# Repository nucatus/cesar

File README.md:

# Cesar 3

**A 42-key ergonomic unibody keyboard, built around a modified Dvorak layout and a layer system designed for programming.**

Cesar 3 is the third iteration of a personal keyboard project. The goal is simple: type and write code all day without straining the hands, wrists or shoulders. Every decision in the design (the splayed key columns, the angled halves, the thumb clusters, the layout and the layers) serves that goal.

---

## Why it's ergonomic

- **Split, angled halves on a single board.** The two hands sit at shoulder-friendly angles, so the wrists stay straight and don't bend outward. It's a unibody, so there's still only one thing to carry and no cable between halves.
- **Column stagger and splay.** Keys follow the natural length of each finger: the middle-finger column sits highest, while the pinky and inner columns drop lower. Each column is also rotated to follow the arc the fingers make when they curl.
- **Fanned thumb clusters.** Each thumb gets three keys arranged on an arc. The thumbs, which do almost nothing on a regular keyboard, now handle Space, Enter, Esc, Tab and all the layer switching.
- **42 keys, no reaching.** With no number row, no function row and no far-away modifiers, every key is at most one row away from home. The rest comes from layers.
- **Home-row modifiers.** Shift, Alt, Ctrl and Cmd sit under the resting fingers (hold `A O E U` / `H T N S`), so shortcuts never need a pinky stretch to the corners.

## Modified Dvorak

The base layer is Dvorak. All the vowels sit on the left home row and the most common consonants on the right, so the hands alternate naturally and the fingers spend most of their time on the home row. A few changes adapt it to this board and to coding:

| Change | Why |
|---|---|
| `;` moved to the top-left and `'` to the bottom-left (swapped vs. standard Dvorak) | `;` is typed far more often than `'` in most languages, so it gets the easier spot |
| `L` and `D` swapped | Puts `L` on the right home row under the index finger |
| `/ = - [ ]` and friends removed from the base layer | They live on the dedicated symbol layer, close to home |
| Left outer column → `⌘C` `⌘V` `⌘Z` | One-key copy, paste and undo |
| Thumb keys are dual-role | Tap for `Esc` / `Enter` / `Space` / `Tab`, hold for a layer |

## Layers

On top of the base layer there are **three layers**, each held from a thumb key, so you never have to remember which layer is "on".

| Layer | Activated by | Contents |
|---|---|---|
| Base | — | Modified Dvorak + home-row mods |
| 1 · Numbers & Navigation | hold `Esc` or `Tab` | Digits on the left, arrows and paging on the right |
| 2 · Programming symbols | hold `Enter` or `Space` | Every bracket, operator and sigil you need for code |
| 3 · Function & media | hold either outer thumb key | `F1`–`F12`, media and volume controls |

### Base

### Layer 1: Numbers & navigation

- The most frequent digits (`0 1 2 3`) sit on the home row under the strongest fingers.
- The arrows go `← ↓ ↑ →` in a single row, the same order as Vim's `h j k l`.
- The layer is held from **either** thumb (`Esc` or `Tab`). While `Tab` holds it, the left thumbs become `Del` and `Backspace`, so you can edit while you navigate.

### Layer 2: Programming symbols

This layer was designed for code:

- **Brackets are on the home row as mirrored pairs:** `{ ( ) } [ ]`. Opening and closing a block is a single roll across the fingers.
- **Operators sit together:** `- * & |` on the right home row and `= + ! $` on the left bottom row, so comparisons (`!=`, `==`, `&&`, `||`, `+=`, `->`) are short rolls.
- **Shell and path characters** (`~ / \ % ^ ` # @ ? _`) all sit within one row of home.
- It can be held from **either** thumb, so you can always use the hand opposite the symbol.

### Layer 3: Function & media

- `F1`–`F12` run along the top two rows, with home-row mods still available. This makes IDE shortcuts like `⇧F6` and `⌘F12` easy to reach.
- Previous, Play/Pause and Next are on the left home row, with volume just below.

### Tuning

The full keymap is in [`firmware/config/boards/shields/cesar/cesar.keymap`](firmware/config/boards/shields/cesar/cesar.keymap).

The home-row mods and layer-taps use ZMK's `balanced` hold-tap with **positional hold-trigger** (a mod only activates when the next key is on the opposite hand). They also use a 280 ms tapping term, a 150 ms `require-prior-idle` and a 175 ms quick-tap. Together these stop accidental modifiers while you type fast.

---

## Hardware

|  |  |
|---|---|
| Keys | 42 (36 alpha + 6 thumb); 40 × 1u, 2 × 1.5u |
| Switches | MX-style, hot-swappable (Kailh sockets) |
| Controller | nice!nano v2 (nRF52840), wireless via Bluetooth |
| Firmware | [ZMK](https://zmk.dev), shield `cesar` (in [`firmware/`](firmware)) |
| Matrix | 4 rows × 12 columns, `col2row`, SOD-123 diodes |
| Extras | Reset button, two indicator LEDs |
| Plates | Top (switch) plate + bottom plate, 304 × 118 mm |
| Design tools | KiCad 9 |

### PCB

The finished board from below, with the Kailh hot-swap sockets and SOD-123 diodes soldered on:

### Schematic

### Plates

The top plate holds the switches; the bottom plate closes the case. Both are ready to cut from the DXF files in [`cad/`](cad).

---

## Repository layout

```
cad/                 Top and bottom plate DXF files (laser / CNC ready)
pcb/                 KiCad project: schematic, PCB layout, project settings
firmware/            ZMK user config with the `cesar` shield and keymap
docs/images/         Images used in this README
```

## Building one

1. Order the PCB from the KiCad project in `pcb/` (export Gerbers from KiCad).
2. Cut the two plates from `cad/*.dxf` (acrylic, aluminium or FR4 all work).
3. Solder the 42 SOD-123 diodes, the hot-swap sockets, the reset button, the LEDs and the nice!nano v2.
4. Build the firmware: every push runs the GitHub Actions workflow, which builds `cesar` for `nice_nano_v2`. Download the `.uf2` from the run's artifacts, double-tap reset, and copy it onto the nice!nano.
5. Mount the plates with standoffs, add switches and keycaps.

## License

- **Hardware** (`pcb/`, `cad/`, and the images and documentation in this repository): Copyright (c) 2024 Alexandru Ionita, licensed under the [CERN Open Hardware Licence Version 2 – Strongly Reciprocal](LICENSE) (CERN-OHL-S-2.0). If you distribute a modified version of the design, or products made from one, you must publish your modified source under the same licence.
- **Firmware** (`firmware/`): [MIT](firmware/LICENSE). The ZMK shield files keep their original copyright from the ZMK Contributors.

Source location: https://github.com/nucatus/cesar

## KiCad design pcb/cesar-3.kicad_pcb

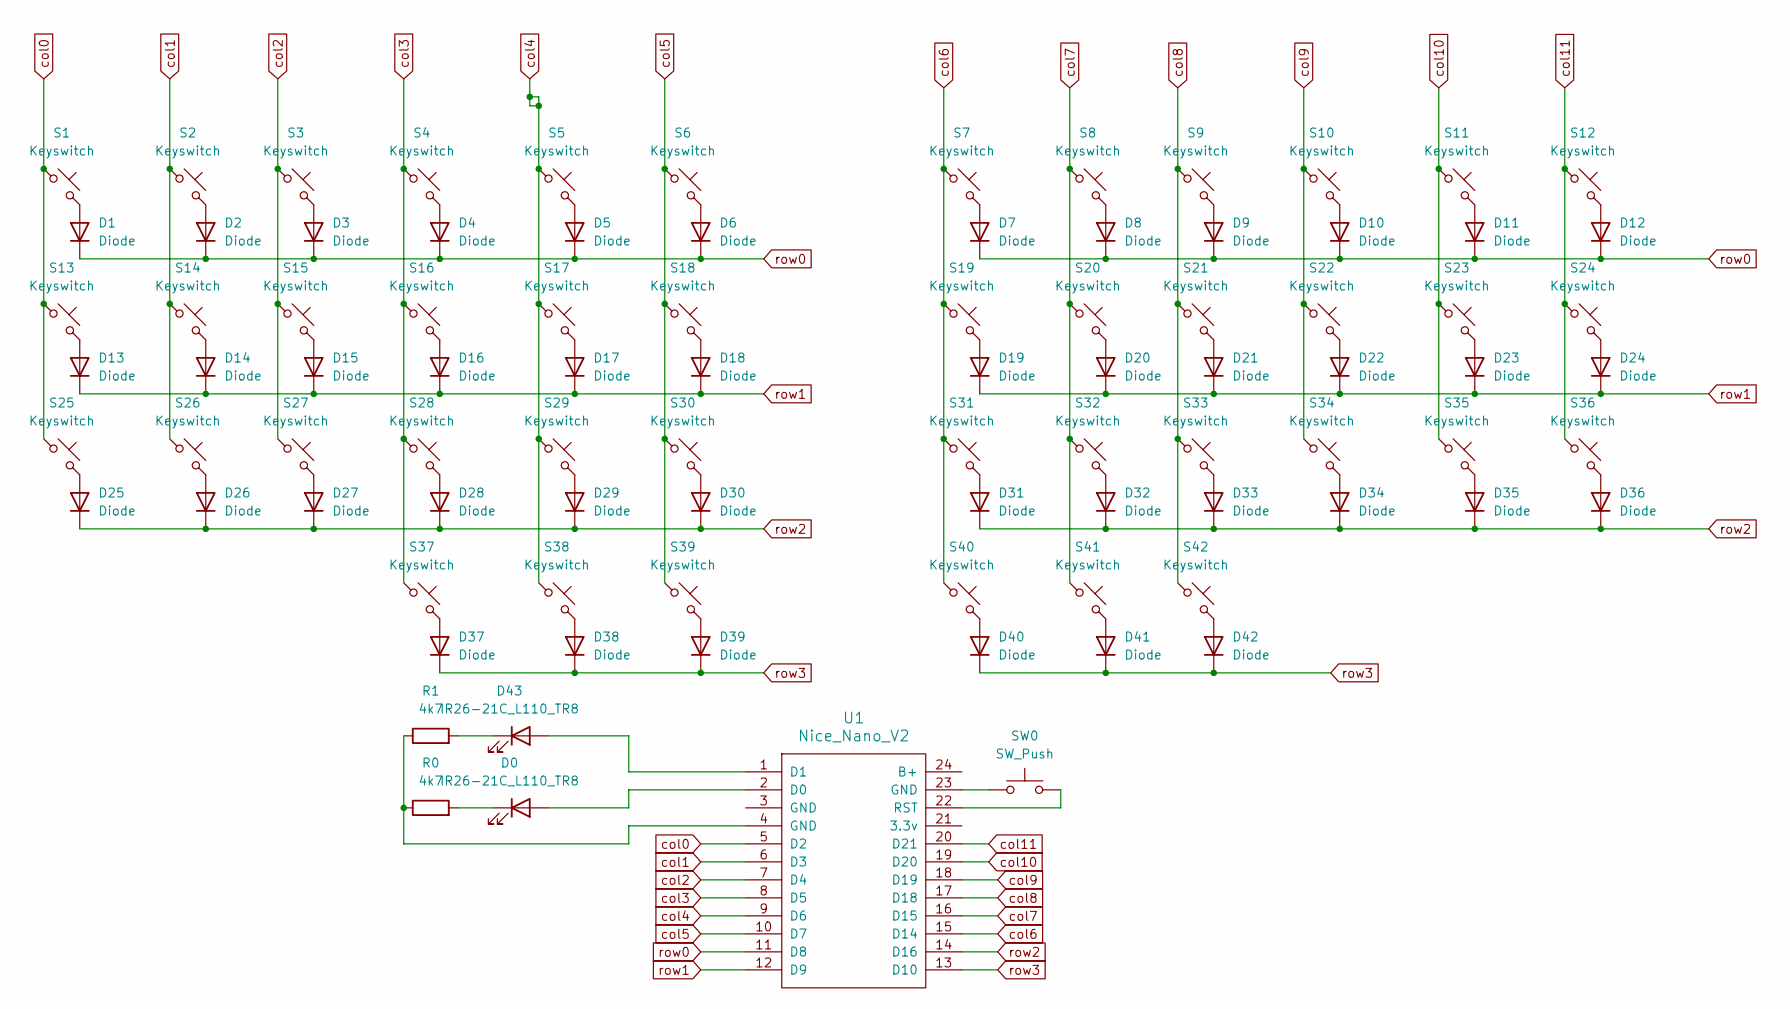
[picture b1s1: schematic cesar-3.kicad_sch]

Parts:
D0, D43: IR26-21C_L110_TR8; LED_1206_3216Metric
D1, D2, D3, D4, D5, D6, D7, D8, D9, D10, D11, D12, D13, D14, D15, D16, D17, D18, D19, D20, D21, D22, D23, D24, D25, D26, D27, D28, D29, D30, D31, D32, D33, D34, D35, D36, D37, D38, D39, D40, D41, D42: Diode; D_SOD-123
R0, R1: 4k7; R_0805_2012Metric
S1, S2, S3, S4, S5, S6, S7, S8, S9, S10, S11, S12, S13, S14, S15, S16, S17, S18, S19, S20, S21, S22, S23, S24, S25, S26, S27, S28, S29, S30, S31, S32, S33, S34, S35, S36, S37, S38, S39, S40, S41, S42: Keyswitch; Hotswap_MX_1.00u
SW0: SW_Push; SW_Tactile_SPST_NO_Straight_CK_PTS636Sx25SMTRLFS
U1: Nice_Nano_V2

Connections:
unnamed: D0.2 (A), U1.2 (D0)
unnamed: D0.1 (K), R0.2
unnamed: D1.2 (A), S1.2
unnamed: D2.2 (A), S2.2
unnamed: D3.2 (A), S3.2
unnamed: D4.2 (A), S4.2
unnamed: D5.2 (A), S5.2
unnamed: D6.2 (A), S6.2
unnamed: D7.2 (A), S7.2
unnamed: D8.2 (A), S8.2
unnamed: D9.2 (A), S9.2
unnamed: D10.2 (A), S10.2
unnamed: D11.2 (A), S11.2
unnamed: D12.2 (A), S12.2
unnamed: D13.2 (A), S13.2
unnamed: D14.2 (A), S14.2
unnamed: D15.2 (A), S15.2
unnamed: D16.2 (A), S16.2
unnamed: D17.2 (A), S17.2
unnamed: D18.2 (A), S18.2
unnamed: D19.2 (A), S19.2
unnamed: D20.2 (A), S20.2
unnamed: D21.2 (A), S21.2
unnamed: D22.2 (A), S22.2
unnamed: D23.2 (A), S23.2
unnamed: D24.2 (A), S24.2
unnamed: D25.2 (A), S25.2
unnamed: D26.2 (A), S26.2
unnamed: D27.2 (A), S27.2
unnamed: D28.2 (A), S28.2
unnamed: D29.2 (A), S29.2
unnamed: D30.2 (A), S30.2
unnamed: D31.2 (A), S31.2
unnamed: D32.2 (A), S32.2
unnamed: D33.2 (A), S33.2
unnamed: D34.2 (A), S34.2
unnamed: D35.2 (A), S35.2
unnamed: D36.2 (A), S36.2
unnamed: D37.2 (A), S37.2
unnamed: D38.2 (A), S38.2
unnamed: D39.2 (A), S39.2
unnamed: D40.2 (A), S40.2
unnamed: D41.2 (A), S41.2
unnamed: D42.2 (A), S42.2
unnamed: D43.2 (A), U1.1 (D1)
unnamed: D43.1 (K), R1.2
unnamed: R0.1, R1.1, U1.4 (GND)
unnamed: SW0.1, U1.23 (GND)
unnamed: SW0.2, U1.22 (RST)
col0: S1.1, S13.1, S25.1, U1.5 (D2)
col1: S2.1, S14.1, S26.1, U1.6 (D3)
col2: S3.1, S15.1, S27.1, U1.7 (D4)
col3: S4.1, S16.1, S28.1, S37.1, U1.8 (D5)
col4: S5.1, S17.1, S29.1, S38.1, U1.9 (D6)
col5: S6.1, S18.1, S30.1, S39.1, U1.10 (D7)
col6: S7.1, S19.1, S31.1, S40.1, U1.15 (D14)
col7: S8.1, S20.1, S32.1, S41.1, U1.16 (D15)
col8: S9.1, S21.1, S33.1, S42.1, U1.17 (D18)
col9: S10.1, S22.1, S34.1, U1.18 (D19)
col10: S11.1, S23.1, S35.1, U1.19 (D20)
col11: S12.1, S24.1, S36.1, U1.20 (D21)
row0: D1.1 (K), D2.1 (K), D3.1 (K), D4.1 (K), D5.1 (K), D6.1 (K), D7.1 (K), D8.1 (K), D9.1 (K), D10.1 (K), D11.1 (K), D12.1 (K), U1.11 (D8)
row1: D13.1 (K), D14.1 (K), D15.1 (K), D16.1 (K), D17.1 (K), D18.1 (K), D19.1 (K), D20.1 (K), D21.1 (K), D22.1 (K), D23.1 (K), D24.1 (K), U1.12 (D9)
row2: D25.1 (K), D26.1 (K), D27.1 (K), D28.1 (K), D29.1 (K), D30.1 (K), D31.1 (K), D32.1 (K), D33.1 (K), D34.1 (K), D35.1 (K), D36.1 (K), U1.14 (D16)
row3: D37.1 (K), D38.1 (K), D39.1 (K), D40.1 (K), D41.1 (K), D42.1 (K), U1.13 (D10)

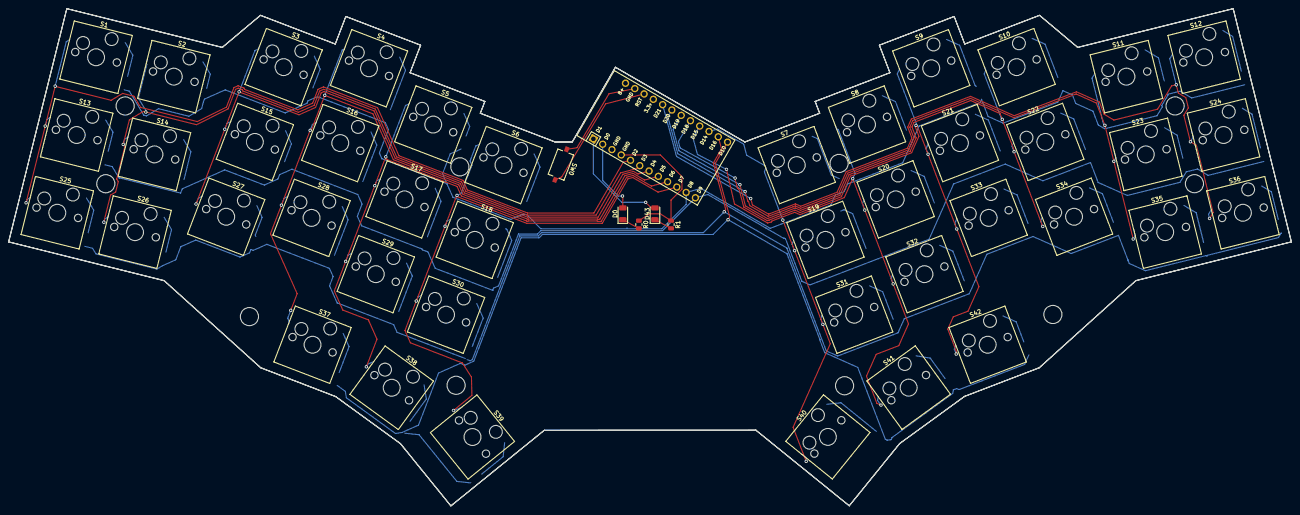
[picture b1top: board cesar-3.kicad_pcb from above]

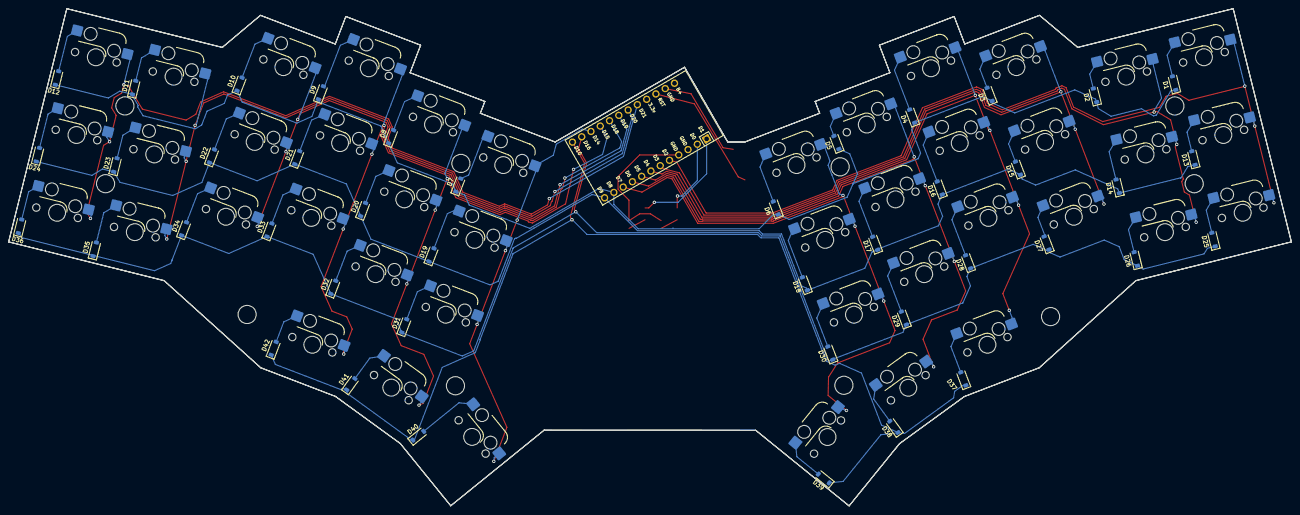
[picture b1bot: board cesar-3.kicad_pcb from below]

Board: 2 copper layers, 304.2 x 117.9 mm, 90 parts (42 on the bottom side), 65 nets.

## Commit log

2023-12-28 before ratation
2023-12-28 after rotarion
2023-12-28 before rotation
2023-12-28 after rotation
2023-12-28 valid after rotation
2023-12-28 routing complete
2024-01-14 Production v0.1 PCB and plate dxf files
    The v0.1 prototype and the dxf files corresponding to the bottom and top
    plates.
2024-02-19 Add README with photos, PCB, schematic, plate and keymap images
    Move the plate DXFs into cad/ and the KiCad project into pcb/.
2024-02-21 Add ZMK firmware config with the cesar shield
    Shield, keymap and nice!nano v2 overlay under firmware/, plus a
    GitHub Actions workflow that builds the firmware with ZMK.
2024-03-04 Add CERN-OHL-S-2.0 hardware and MIT firmware licenses
2024-03-09 Show both thumb keys that activate the num and sym layers
